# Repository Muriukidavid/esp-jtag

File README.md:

This is a JTAG programmer for esp targets based on esp-prog redone in Kicad.

The goal of this repo is to enable customization by adding or removing features. Feel welcome to fork the repo and share back your customizations through a pull request.

### Features:
* FT2232H based
* Esp Jtag programming
* A separate serial port for debug
* SN74AH buffers for JTAG IO pins(5V/3V torelant)
* Rx/Tx status LEDs
* Autoprogram using RTS and DTS signals

### TODO
* <s>Layout the PCB and route</s>
- <s>Add LCSC.com BOM column</s> 
* Add digikey BOM column
<br/>

### Schematic

### Board 3D Top View 

A preview of the on-going PCB layout design

3D TOP view 

3D ISO view 

### BOM
<a href="bom/ibom.html" rel="BOM">

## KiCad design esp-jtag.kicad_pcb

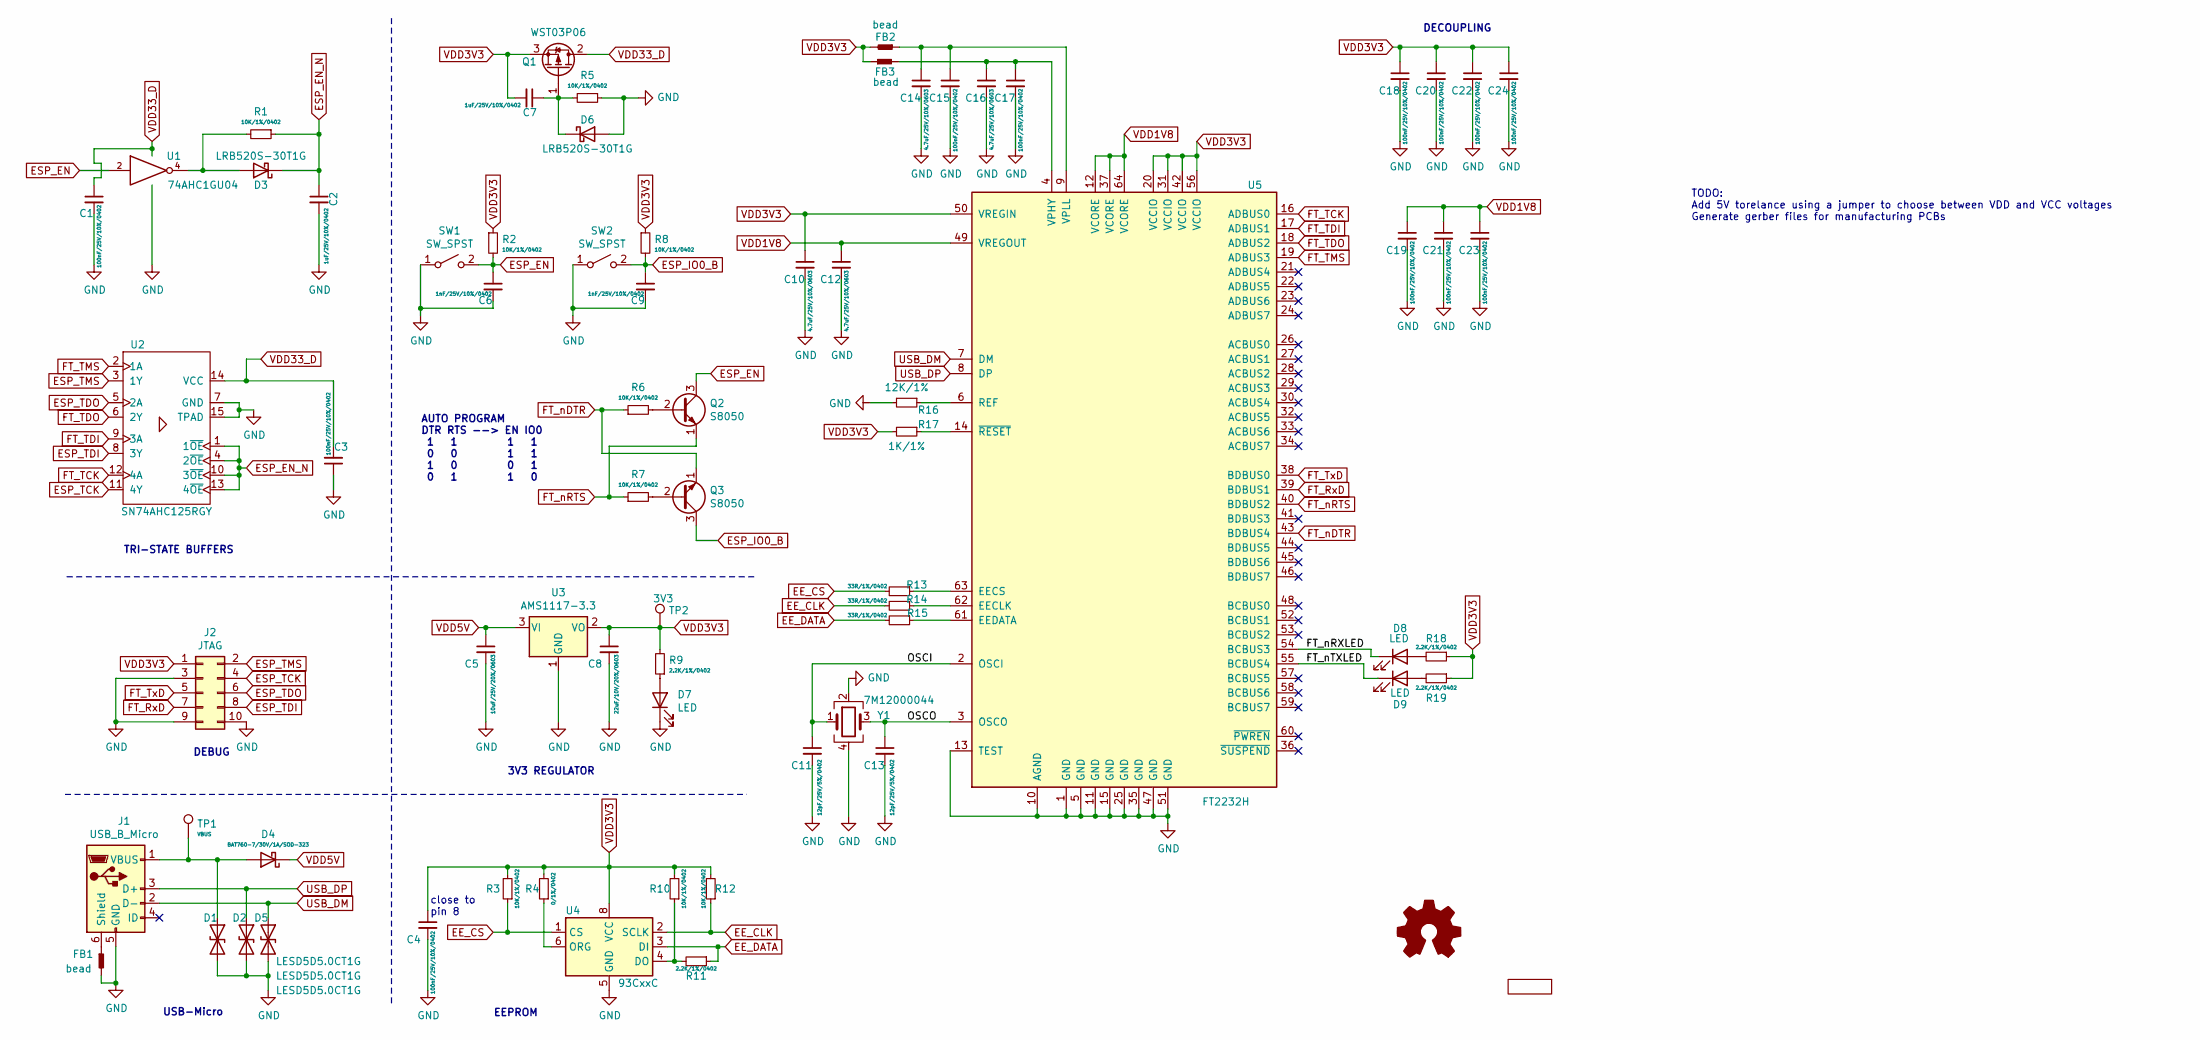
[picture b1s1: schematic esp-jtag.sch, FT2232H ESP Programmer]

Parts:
C1, C3, C4, C15, C17, C18, C19, C20, C21, C22, C23, C24: 100nF/25V/10%/0402; C_0402_1005Metric; Mfr # GRM155R71E104KE14D; LCSC # C77014
C2, C7: 1uF/25V/10%/0402; C_0402_1005Metric; Mfr # C1005X5R1E105KT000E; LCSC # C191909
C5: 10uF/25V/20%/0603; C_0603_1608Metric; Mfr # GRM188R61E106MA73D; LCSC # C91606
C6, C9: 1nF/25V/10%/0402; C_0402_1005Metric; Mfr # GRM155B11E102KA01D; LCSC # C162149
C8: 22uF/10V/20%/0603; C_0603_1608Metric; Mfr # GRM188R61A226ME15D; LCSC # C84419
C10, C12, C14, C16: 4.7uF/25V/10%/0603; C_0603_1608Metric; Mfr # GRM188R61E475KE15D; LCSC # C408137
C11, C13: 12pF/25V/5%/0402; C_0402_1005Metric; Mfr # GRM1555C1E120JA01D; LCSC # C161514
D1, D2, D5: LESD5D5.0CT1G; D_SOD-523; Mfr # LESD5D5.0CT1G; LCSC # C383211
D3, D6: LRB520S-30T1G; D_SOD-523; Mfr # LRB520S-30T1G; LCSC # C83680
D4: BAT760-7/30V/1A/SOD-323; D_SOD-323; Mfr # BAT760-7; LCSC # C124187
D7: LED; LED_0402_1005Metric; Mfr # FC-F1005HRK-620H5; LCSC # C130719
D8: LED; LED_0402_1005Metric; Mfr # BL-HB337A-AV-TRB; LCSC # C165977
D9: LED; LED_0402_1005Metric; Mfr # BL-HGE37A-AV-TRB; LCSC # C165979
FB1, FB2, FB3: bead; L_0805_2012Metric; Mfr # BLM21AG601SN1D; LCSC # C85837
J1: USB_B_Micro; USB_Micro-B_Molex_47346-0001; Mfr # 47346-0001; LCSC # C132560
J2: JTAG; PinHeader_2x05_P1.27mm_Vertical_SMD
L1: karibe_logo
Q1: WST03P06; SOT-23; Mfr # WST03P06; LCSC # C105166
Q2, Q3: S8050; SOT-23; Mfr # S8050; LCSC # C2146
R1, R2, R3, R5, R6, R7, R8, R10, R12: 10K/1%/0402; R_0402_1005Metric; Mfr # RC0402FR-0710KL; LCSC # C60490
R4: 0/1%/0402; R_0402_1005Metric; Mfr # RC0402FR-070RL; LCSC # C106231
R9, R11, R18, R19: 2.2K/1%/0402; R_0402_1005Metric; Mfr # RC0402FR-072K2L; LCSC # C114762
R13, R14, R15: 33R/1%/0402; R_0402_1005Metric; Mfr # 0402WGF330JTCE; LCSC # C25105
R16: 12K/1%; R_0402_1005Metric; Mfr # RC0402FR-0712KL; LCSC # C114760
R17: 1K/1%; R_0402_1005Metric; Mfr # RC0402FR-071KL; LCSC # C106235
SW1, SW2: SW_SPST; SW_SPST_PTS810; Mfr # PTS810SJG250SMTRLFS; LCSC # C221895
TP1: VBUS; TestPoint_Loop_D1.80mm_Drill1.0mm_Beaded; Mfr # 5001; LCSC # C238122
TP2: 3V3; TestPoint_Loop_D1.80mm_Drill1.0mm_Beaded; Mfr # 5001; LCSC # C238122
U1: 74AHC1GU04; SOT-353_SC-70-5; Mfr # 74AHC1GU04GW,125; LCSC # C5514
U2: SN74AHC125RGY; VQFN-14_3.6x3.6x05P; Mfr # SN74AHC125RGY; LCSC # C181604
U3: AMS1117-3.3; SOT-223-3_TabPin2; Mfr # AMS1117-3.3; LCSC # C6186
U4: 93CxxC; SOIC-8_150mil; Mfr # M93C46-WMN6TP; LCSC # C7565
U5: FT2232H; LQFP-64_10x10mm_P0.5mm; Mfr # FT2232HL-REEL; LCSC # C27882
Y1: 7M12000044; Crystal_SMD_3225-4Pin_3.2x2.5mm; Mfr # 7M12000044; LCSC # C93114

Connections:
/FT_nRXLED: D8.1 (K), U5.54 (BCBUS3)
/FT_nTXLED: D9.1 (K), U5.55 (BCBUS4)
/OSCI: C11.1, U5.2 (OSCI), Y1.1
/OSCO: C13.1, U5.3 (OSCO), Y1.3
EE_CLK: R12.1, R14.2, U4.2 (SCLK)
EE_CS: R3.1, R13.2, U4.1 (CS)
EE_DATA: R11.1, R15.2, U4.3 (DI)
ESP_EN: C6.1, Q2.3 (C), R2.2, SW1.2 (B), U1.2
ESP_EN_N: C2.1, D3.1 (K), R1.1, U2.1 (1~OE), U2.4 (2~OE), U2.10 (3~OE), U2.13 (4~OE)
ESP_IO0_B: C9.1, Q3.3 (C), R8.2, SW2.2 (B)
ESP_TCK: J2.4, U2.11 (4Y)
ESP_TDI: J2.8, U2.8 (3Y)
ESP_TDO: J2.6, U2.5 (2A)
ESP_TMS: J2.2, U2.3 (1Y)
FT_RxD: J2.7, U5.39 (BDBUS1)
FT_TCK: U2.12 (4A), U5.16 (ADBUS0)
FT_TDI: U2.9 (3A), U5.17 (ADBUS1)
FT_TDO: U2.6 (2Y), U5.18 (ADBUS2)
FT_TMS: U2.2 (1A), U5.19 (ADBUS3)
FT_TxD: J2.5, U5.38 (BDBUS0)
FT_nDTR: Q3.1 (E), R6.1, U5.43 (BDBUS4)
FT_nRTS: Q2.1 (E), R7.1, U5.40 (BDBUS2)
GND: C1.2, C2.2, C3.1, C4.2, C5.2, C6.2, C8.2, C9.2, C10.2, C11.2, C12.2, C13.2, C14.2, C15.2, C16.2, C17.2, C18.2, C19.2, C20.2, C21.2, C22.2, C23.2, C24.2, D1.2 (A2), D2.2 (A2), D5.2 (A2), D6.2 (A), D7.1 (K), FB1.2, J1.5 (GND), J2.3, J2.9, J2.10, R5.1, R16.2, SW1.1 (A), SW2.1 (A), U1.3 (GND), U2.7 (GND), U2.15 (TPAD), U3.1 (GND), U4.5 (GND), U5.1 (GND), U5.5 (GND), U5.10 (AGND), U5.11 (GND), U5.13 (TEST), U5.15 (GND), U5.25 (GND), U5.35 (GND), U5.47 (GND), U5.51 (GND), Y1.2, Y1.4
unnamed: C7.1, D6.1 (K), Q1.1 (G), R5.2
unnamed: C14.1, C15.1, FB2.1, U5.9 (VPLL)
unnamed: C16.1, C17.1, FB3.2, U5.4 (VPHY)
unnamed: D1.1 (A1), D4.2 (A), J1.1 (VBUS), TP1.1
unnamed: D3.2 (A), R1.2, U1.4
unnamed: D7.2 (A), R9.1
unnamed: D8.2 (A), R18.2
unnamed: D9.2 (A), R19.2
unnamed: FB1.1, J1.6 (Shield)
unnamed: Q2.2 (B), R6.2
unnamed: Q3.2 (B), R7.2
unnamed: R4.1, U4.6 (ORG)
unnamed: R10.1, R11.2, U4.4 (DO)
unnamed: R13.1, U5.63 (EECS)
unnamed: R14.1, U5.62 (EECLK)
unnamed: R15.1, U5.61 (EEDATA)
unnamed: R16.1, U5.6 (REF)
unnamed: R17.1, U5.14 (~RESET)
USB_DM: D5.1 (A1), J1.2 (D-), U5.7 (DM)
USB_DP: D2.1 (A1), J1.3 (D+), U5.8 (DP)
VDD1V8: C12.1, C19.1, C21.1, C23.1, U5.12 (VCORE), U5.37 (VCORE), U5.49 (VREGOUT), U5.64 (VCORE)
VDD3V3: C4.1, C7.2, C8.1, C10.1, C18.1, C20.1, C22.1, C24.1, FB2.2, FB3.1, J2.1, Q1.3 (S), R2.1, R3.2, R4.2, R8.1, R9.2, R10.2, R12.2, R17.2, R18.1, R19.1, TP2.1, U3.2 (VO), U4.8 (VCC), U5.20 (VCCIO), U5.31 (VCCIO), U5.42 (VCCIO), U5.50 (VREGIN), U5.56 (VCCIO)
VDD5V: C5.1, D4.1 (K), U3.3 (VI)
VDD33_D: C1.1, C3.2, Q1.2 (D), U1.5 (VCC), U2.14 (VCC)

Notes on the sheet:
close to pin 8
EEPROM
USB-Micro
3V3 REGULATOR
DECOUPLING
DEBUG
TRI-STATE BUFFERS
AUTO PROGRAM DTR RTS --> EN IO0 1 1 1 1 0 0 1 1 1 0 0 1 0 1 1 0
TODO: Add 5V torelance using a jumper to choose between VDD and VCC voltages Generate gerber files for manufacturing PCBs

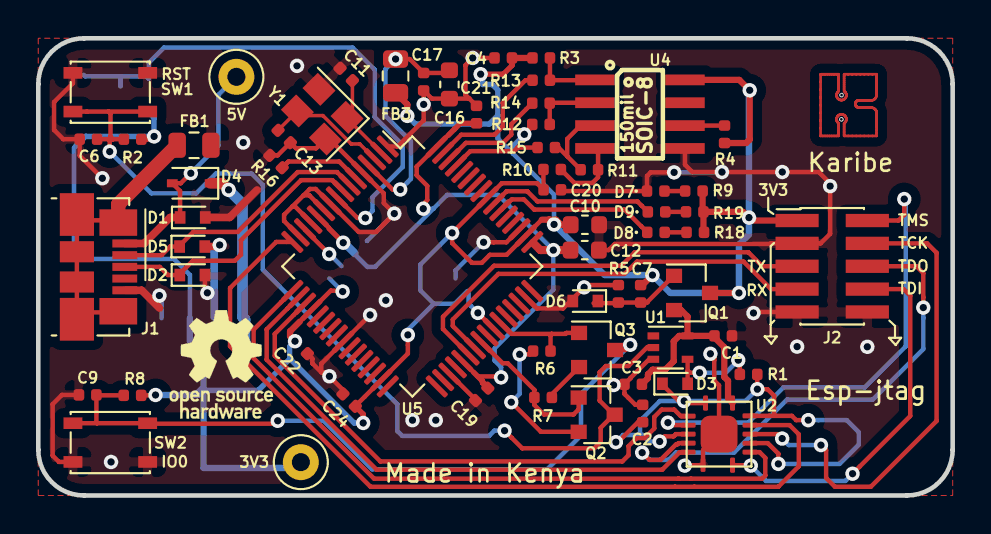
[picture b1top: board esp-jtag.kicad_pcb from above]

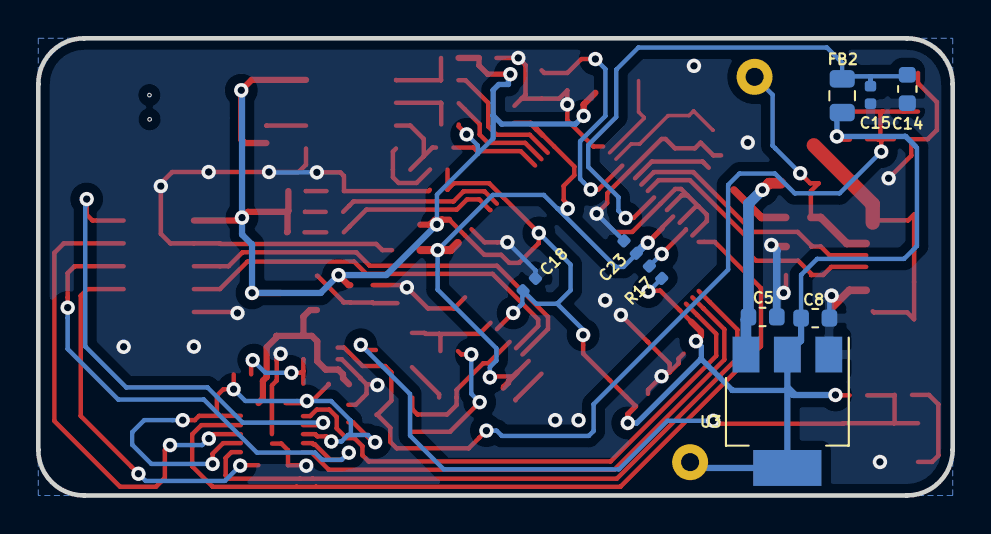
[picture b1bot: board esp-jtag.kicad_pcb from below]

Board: 2 copper layers, 50.8 x 25.4 mm, 71 parts (9 on the bottom side), 47 nets.

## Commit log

2019-10-22 Add initial revision
    Create a kicad project for the programmer
    Capture a schematic based on esp-prog schematic
    Add manufacturer part number and LCSC part number to all components in the schematic
    Associate all components with correct(hopefully) footprints
    Add missing/custom footprints and 3D models
    export a HTML BOM
2019-10-23 Layout and route the PCB
    Prepare the PCB layout by arranging the components
    Route all traces and rectify mistakes in the connections
    Add ground pours on top and bottom copper
    Update the preview images and the README file
2020-07-23 Minor tweaks
    Finalize PCB layout, especially top silkscreen
    Export ray-tracing renders
    Update the README file
